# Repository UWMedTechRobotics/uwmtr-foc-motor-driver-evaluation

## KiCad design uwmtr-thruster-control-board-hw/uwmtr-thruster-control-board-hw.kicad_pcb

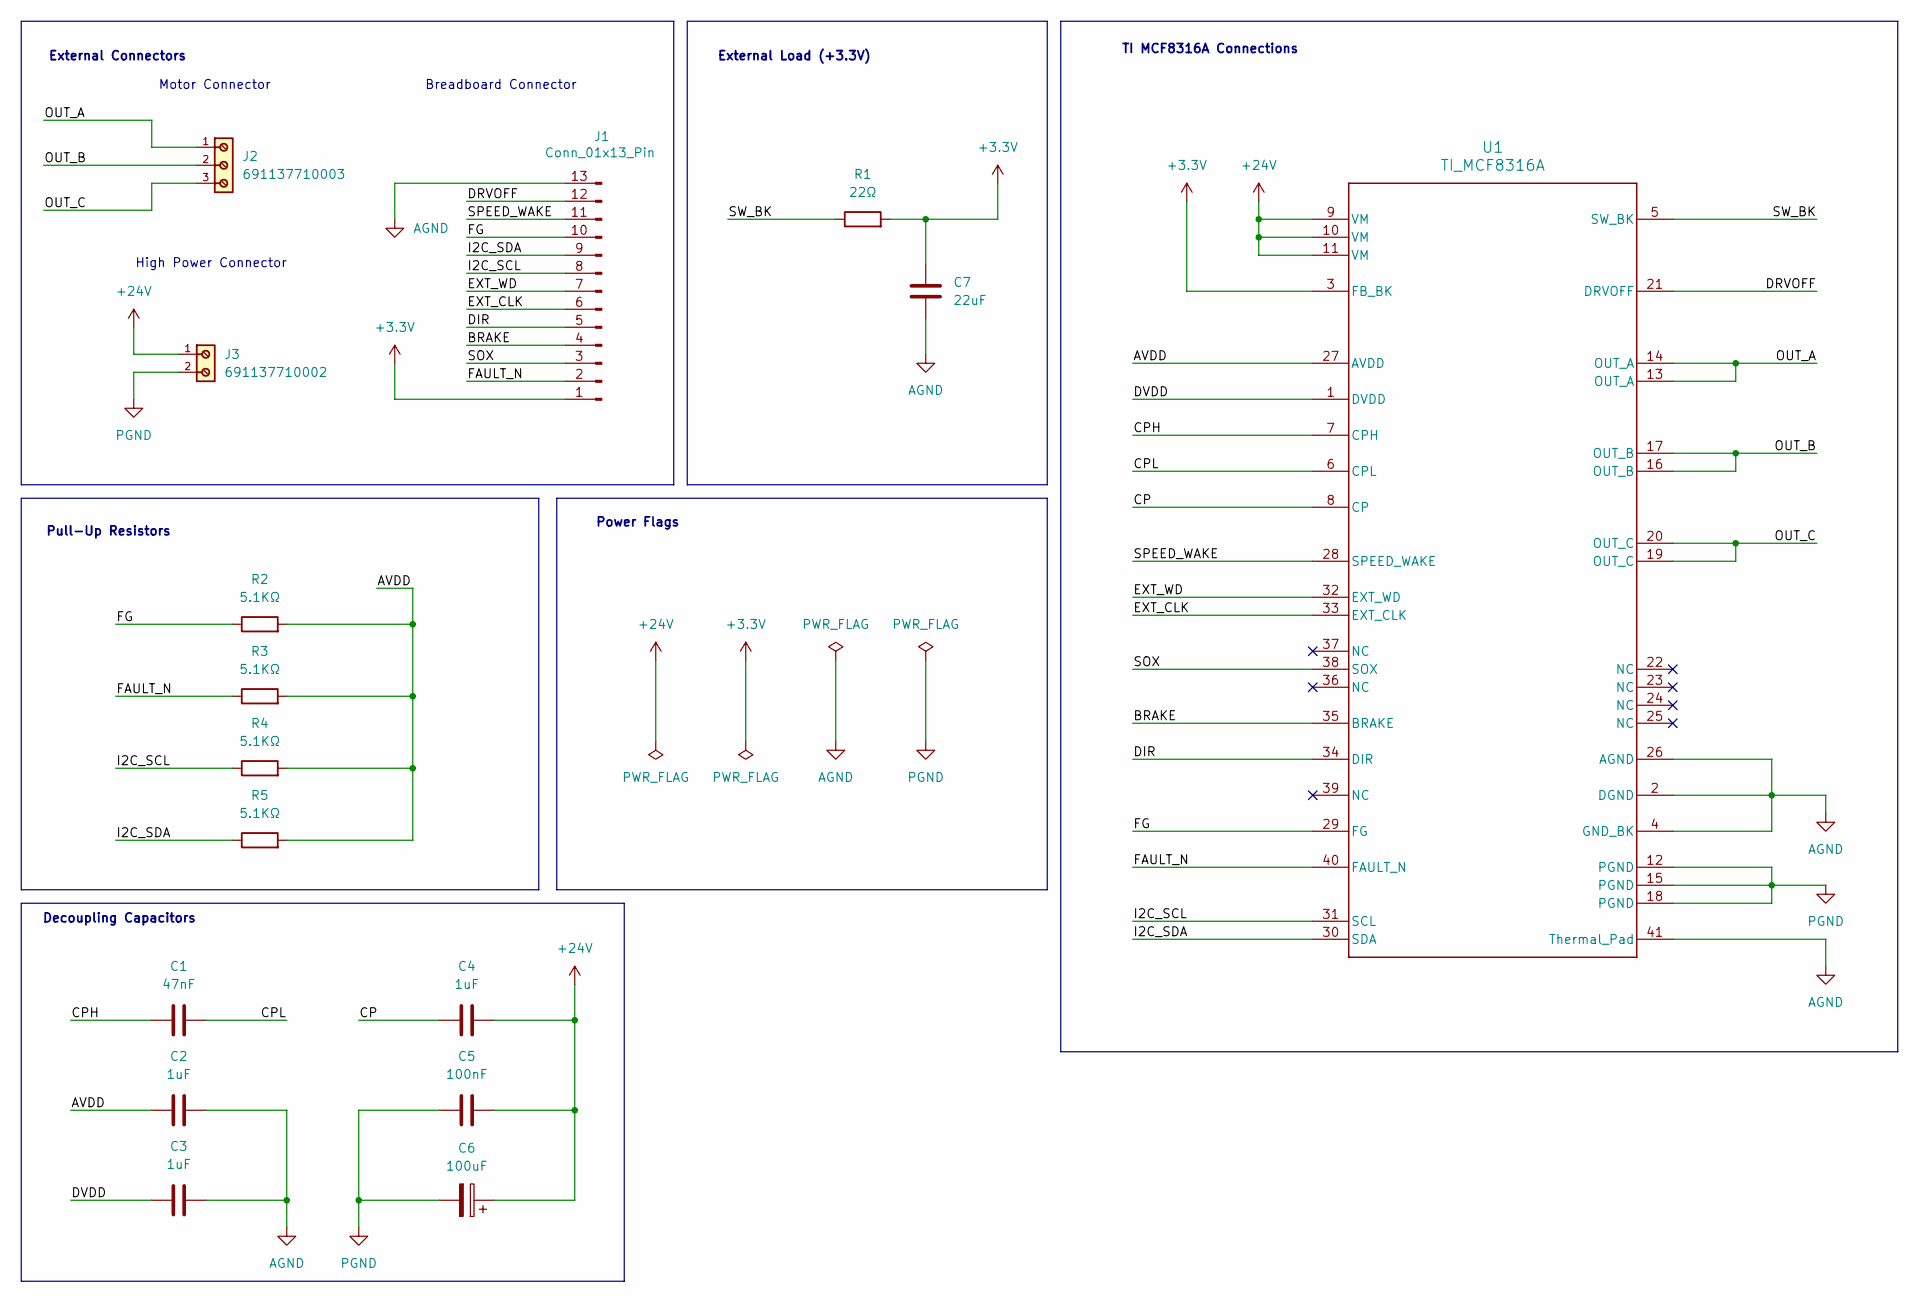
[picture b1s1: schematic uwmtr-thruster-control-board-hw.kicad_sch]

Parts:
C1: 47nF; C_0603_1608Metric; MFR.Part # CL10B473KB8NNNC; JLCPCB Part # C1622
C2, C3, C4: 1uF; C_0603_1608Metric; MFR.Part # CL10A105KB8NNNC; JLCPCB Part # C15849
C5: 100nF; C_0603_1608Metric; MFR.Part # CC0603KRX7R9BB104; JLCPCB Part # C14663
C6: 100uF; C_Radial_D8.0mm_H11.5mm_P3.50mm; JLCPCB Part # C2749
C7: 22uF; C_0603_1608Metric; MFR.Part # CL10A226MQ8NRNC; JLCPCB Part # C59461
J1: Conn_01x13_Pin; PinSocket_1x13_P2.54mm_Vertical
J2: 691137710003
J3: 691137710002
R1: 22Ω; R_1206_3216Metric; MFR.Part # 1206W4F220JT5E; JLCPCB Part # C17958
R2, R3, R4, R5: 5.1KΩ; R_0603_1608Metric; MFR.Part # 0603WAF5101T5E; JLCPCB Part # C23186
U1: TI_MCF8316A; JLCPCB Part # C3681167

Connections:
+3.3V: C7.2, J1.1 (Pin_13), R1.2, U1.3 (FB_BK)
+24V: C4.2, C5.2, C6.1, J3.1, U1.9 (VM), U1.10 (VM), U1.11 (VM)
/AVDD: C2.1, R2.2, R3.2, R4.2, R5.2, U1.27 (AVDD)
/BRAKE: J1.4 (Pin_10), U1.35 (BRAKE)
/CP: C4.1, U1.8 (CP)
/CPH: C1.1, U1.7 (CPH)
/CPL: C1.2, U1.6 (CPL)
/DIR: J1.5 (Pin_9), U1.34 (DIR)
/DRVOFF: J1.12 (Pin_2), U1.21 (DRVOFF)
/DVDD: C3.1, U1.1 (DVDD)
/EXT_CLK: J1.6 (Pin_8), U1.33 (EXT_CLK)
/EXT_WD: J1.7, U1.32 (EXT_WD)
/FAULT_N: J1.2 (Pin_12), R3.1, U1.40 (FAULT_N)
/FG: J1.10 (Pin_4), R2.1, U1.29 (FG)
/I2C_SCL: J1.8 (Pin_6), R4.1, U1.31 (SCL)
/I2C_SDA: J1.9 (Pin_5), R5.1, U1.30 (SDA)
/OUT_A: J2.1, U1.13 (OUT_A), U1.14 (OUT_A)
/OUT_B: J2.2, U1.16 (OUT_B), U1.17 (OUT_B)
/OUT_C: J2.3, U1.19 (OUT_C), U1.20 (OUT_C)
/SOX: J1.3 (Pin_11), U1.38 (SOX)
/SPEED_WAKE: J1.11 (Pin_3), U1.28 (SPEED_WAKE)
/SW_BK: R1.1, U1.5 (SW_BK)
AGND: C2.2, C3.2, C7.1, J1.13 (Pin_1), U1.2 (DGND), U1.4 (GND_BK), U1.26 (AGND), U1.41 (Thermal_Pad)
PGND: C5.1, C6.2, J3.2, U1.12 (PGND), U1.15 (PGND), U1.18 (PGND)

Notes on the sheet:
High Power Connector
Decoupling Capacitors
External Connectors
Power Flags
Pull-Up Resistors
TI MCF8316A Connections
Motor Connector
Breadboard Connector
External Load (+3.3V)

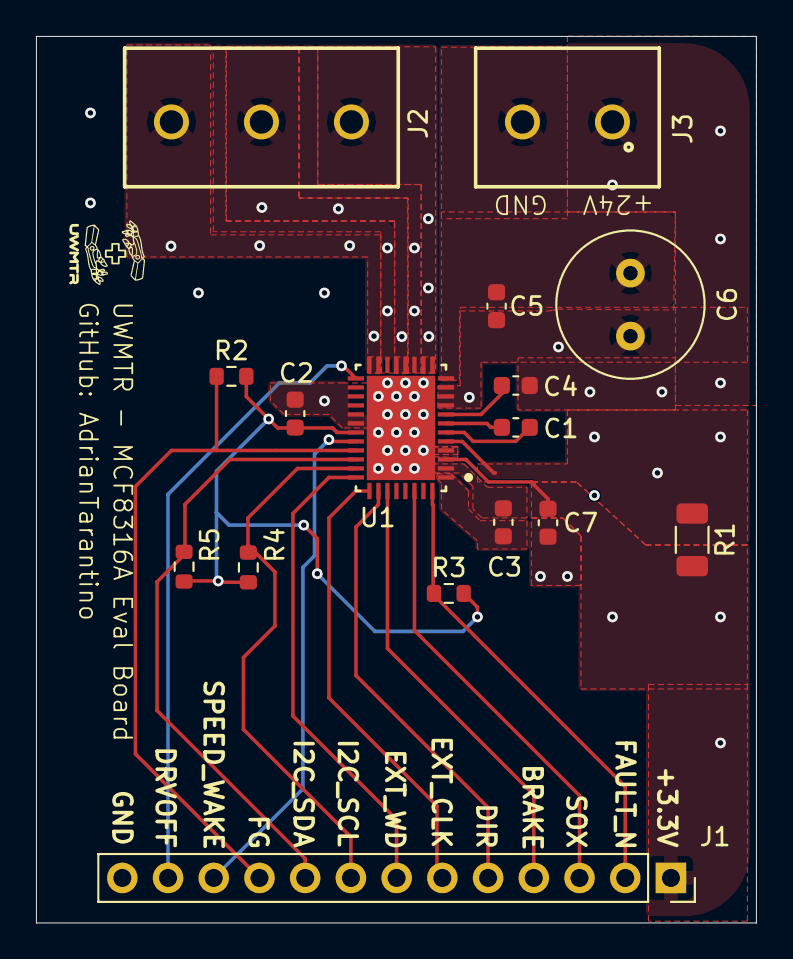
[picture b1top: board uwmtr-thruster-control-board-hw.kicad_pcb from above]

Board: 4 copper layers, 40.0 x 49.2 mm, 16 parts (0 on the bottom side), 24 nets.
